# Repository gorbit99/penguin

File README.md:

# Penguin
## A Redox compatible low profile keyboard with per-key RGB

### Parts

- Kailh Choc Switches x 70
- Kailh Choc Keycaps x 70
- Sk6812 mini-e RGB LED\* x 70
- 1n4148 smt sod-123 package diode x 70
- TRRS connector x 2
- 4 pin through-hole tactile switch x 2
- 680 ohm 0608 package resistor\*\* x 2
- Arduino Pro Micro x 2
- TRRS cable x 1
- USB cable for the arduino x 1

\* The type I designed the keyboard for doesn't match the datasheet exactly for
whatever reason, [try getting something that looks like this one](https://www.aliexpress.com/item/4000475685852.html)

\*\* Should work without any resistors if you just bridge their place instead,
but no guarantees

### Keymaps

Should work with any keymap that was made for the redox series.

### Assembly

The keyboard PCB, just like the Redox PCB is double sided. The only component
that goes on the backside are the diodes. This was done to make the board itself
as thin as possible. The rest of the components mount on the topside.

Start with the microcontroller, the resistor and the RGBs. This is necessary,
because soldering the RGB LEDs can be finicky and you'll want a way to test if
you've connected them successfully, which can be done by flashing the
microcontroller. Check each time that's the switches can sit flush on top of the
LEDs, otherwise the whole switch might end up crooked. 

Afterwards it's best to go from smallest to biggest like usual, first the diodes
on the back, then the tactile switch and the TRRS connector and finally the
switches themselves.

### Flashing

By default the keyboard is set to use EEPROM handedness check, this means that
for the first time for both halves the following commands need to be used:

```
make penguin:default:avrdude-split-left
make penguin:default:avrdude-split-right
```

afterwards the end part can be dropped, when flashing again.

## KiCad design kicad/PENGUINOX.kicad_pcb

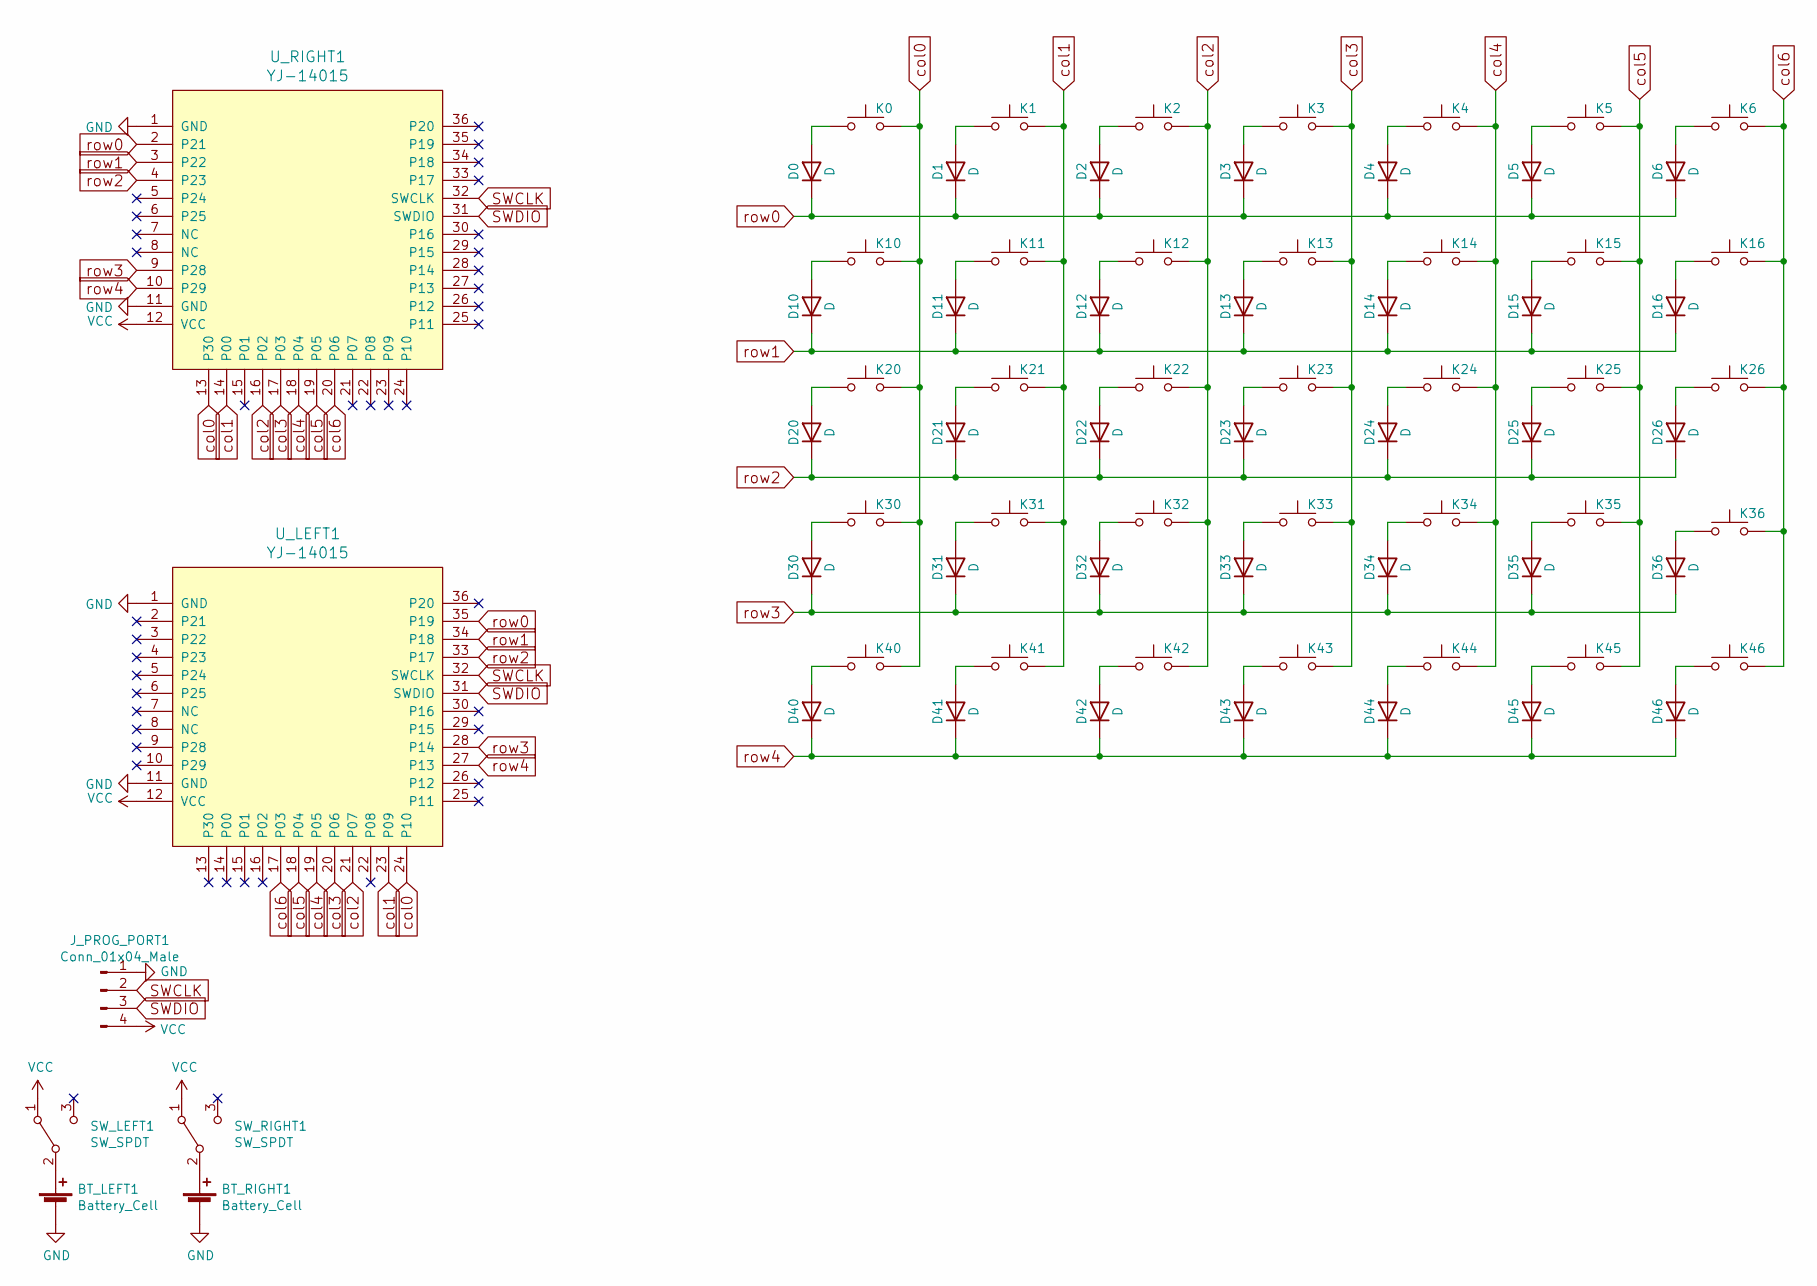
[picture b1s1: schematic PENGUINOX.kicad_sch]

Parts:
BT_LEFT1: Battery_Cell; BatteryHolder_Keystone_3034_1x20mm_bigger_pads
BT_RIGHT1: Battery_Cell; BatteryHolder_Keystone_3034_1x20mm_bigger_pads
D0, D1, D2, D3, D4, D5, D6, D10, D11, D12, D13, D14, D15, D16, D20, D21, D22, D23, D24, D25, D26, D30, D31, D32, D33, D34, D35, D36, D40, D41, D42, D43, D44, D45, D46: D; Diode-dual
J_PROG_PORT1: Conn_01x04_Male; PinHeader_1x04_P2.54mm_Horizontal
K0, K1, K2, K3, K4, K5, K6, K10, K11, K12, K13, K14, K15, K16, K20, K21, K22, K23, K24, K25, K26, K30, K31, K32, K33, K34, K35, K36, K40, K41, K42, K43, K44, K45, K46: KEYSW; Choc_PG1350_Choc_Spacing_Reversible
SW_LEFT1: SW_SPDT; SW_SPDT_PCM12
SW_RIGHT1: SW_SPDT; SW_SPDT_PCM12
U_LEFT1: YJ-14015
U_RIGHT1: YJ-14015

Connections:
GND: BT_LEFT1.2 (-), BT_RIGHT1.2 (-), J_PROG_PORT1.1, U_LEFT1.1 (GND), U_LEFT1.11 (GND), U_RIGHT1.1 (GND), U_RIGHT1.11 (GND)
unnamed: BT_LEFT1.1 (+), SW_LEFT1.2 (B)
unnamed: BT_RIGHT1.1 (+), SW_RIGHT1.2 (B)
unnamed: D0.2 (A), K0.1
unnamed: D1.2 (A), K1.1
unnamed: D2.2 (A), K2.1
unnamed: D3.2 (A), K3.1
unnamed: D4.2 (A), K4.1
unnamed: D5.2 (A), K5.1
unnamed: D6.2 (A), K6.1
unnamed: D10.2 (A), K10.1
unnamed: D11.2 (A), K11.1
unnamed: D12.2 (A), K12.1
unnamed: D13.2 (A), K13.1
unnamed: D14.2 (A), K14.1
unnamed: D15.2 (A), K15.1
unnamed: D16.2 (A), K16.1
unnamed: D20.2 (A), K20.1
unnamed: D21.2 (A), K21.1
unnamed: D22.2 (A), K22.1
unnamed: D23.2 (A), K23.1
unnamed: D24.2 (A), K24.1
unnamed: D25.2 (A), K25.1
unnamed: D26.2 (A), K26.1
unnamed: D30.2 (A), K30.1
unnamed: D31.2 (A), K31.1
unnamed: D32.2 (A), K32.1
unnamed: D33.2 (A), K33.1
unnamed: D34.2 (A), K34.1
unnamed: D35.2 (A), K35.1
unnamed: D36.2 (A), K36.1
unnamed: D40.2 (A), K40.1
unnamed: D41.2 (A), K41.1
unnamed: D42.2 (A), K42.1
unnamed: D43.2 (A), K43.1
unnamed: D44.2 (A), K44.1
unnamed: D45.2 (A), K45.1
unnamed: D46.2 (A), K46.1
SWCLK: J_PROG_PORT1.2, U_LEFT1.32 (SWCLK), U_RIGHT1.32 (SWCLK)
SWDIO: J_PROG_PORT1.3, U_LEFT1.31 (SWDIO), U_RIGHT1.31 (SWDIO)
VCC: J_PROG_PORT1.4, SW_LEFT1.1 (A), SW_RIGHT1.1 (A), U_LEFT1.12 (VCC), U_RIGHT1.12 (VCC)
col0: K0.2, K10.2, K20.2, K30.2, K40.2, U_LEFT1.24 (P10), U_RIGHT1.13 (P30)
col1: K1.2, K11.2, K21.2, K31.2, K41.2, U_LEFT1.23 (P09), U_RIGHT1.14 (P00)
col2: K2.2, K12.2, K22.2, K32.2, K42.2, U_LEFT1.21 (P07), U_RIGHT1.16 (P02)
col3: K3.2, K13.2, K23.2, K33.2, K43.2, U_LEFT1.20 (P06), U_RIGHT1.17 (P03)
col4: K4.2, K14.2, K24.2, K34.2, K44.2, U_LEFT1.19 (P05), U_RIGHT1.18 (P04)
col5: K5.2, K15.2, K25.2, K35.2, K45.2, U_LEFT1.18 (P04), U_RIGHT1.19 (P05)
col6: K6.2, K16.2, K26.2, K36.2, K46.2, U_LEFT1.17 (P03), U_RIGHT1.20 (P06)
row0: D0.1 (K), D1.1 (K), D2.1 (K), D3.1 (K), D4.1 (K), D5.1 (K), D6.1 (K), U_LEFT1.35 (P19), U_RIGHT1.2 (P21)
row1: D10.1 (K), D11.1 (K), D12.1 (K), D13.1 (K), D14.1 (K), D15.1 (K), D16.1 (K), U_LEFT1.34 (P18), U_RIGHT1.3 (P22)
row2: D20.1 (K), D21.1 (K), D22.1 (K), D23.1 (K), D24.1 (K), D25.1 (K), D26.1 (K), U_LEFT1.33 (P17), U_RIGHT1.4 (P23)
row3: D30.1 (K), D31.1 (K), D32.1 (K), D33.1 (K), D34.1 (K), D35.1 (K), D36.1 (K), U_LEFT1.28 (P14), U_RIGHT1.9 (P28)
row4: D40.1 (K), D41.1 (K), D42.1 (K), D43.1 (K), D44.1 (K), D45.1 (K), D46.1 (K), U_LEFT1.27 (P13), U_RIGHT1.10 (P29)

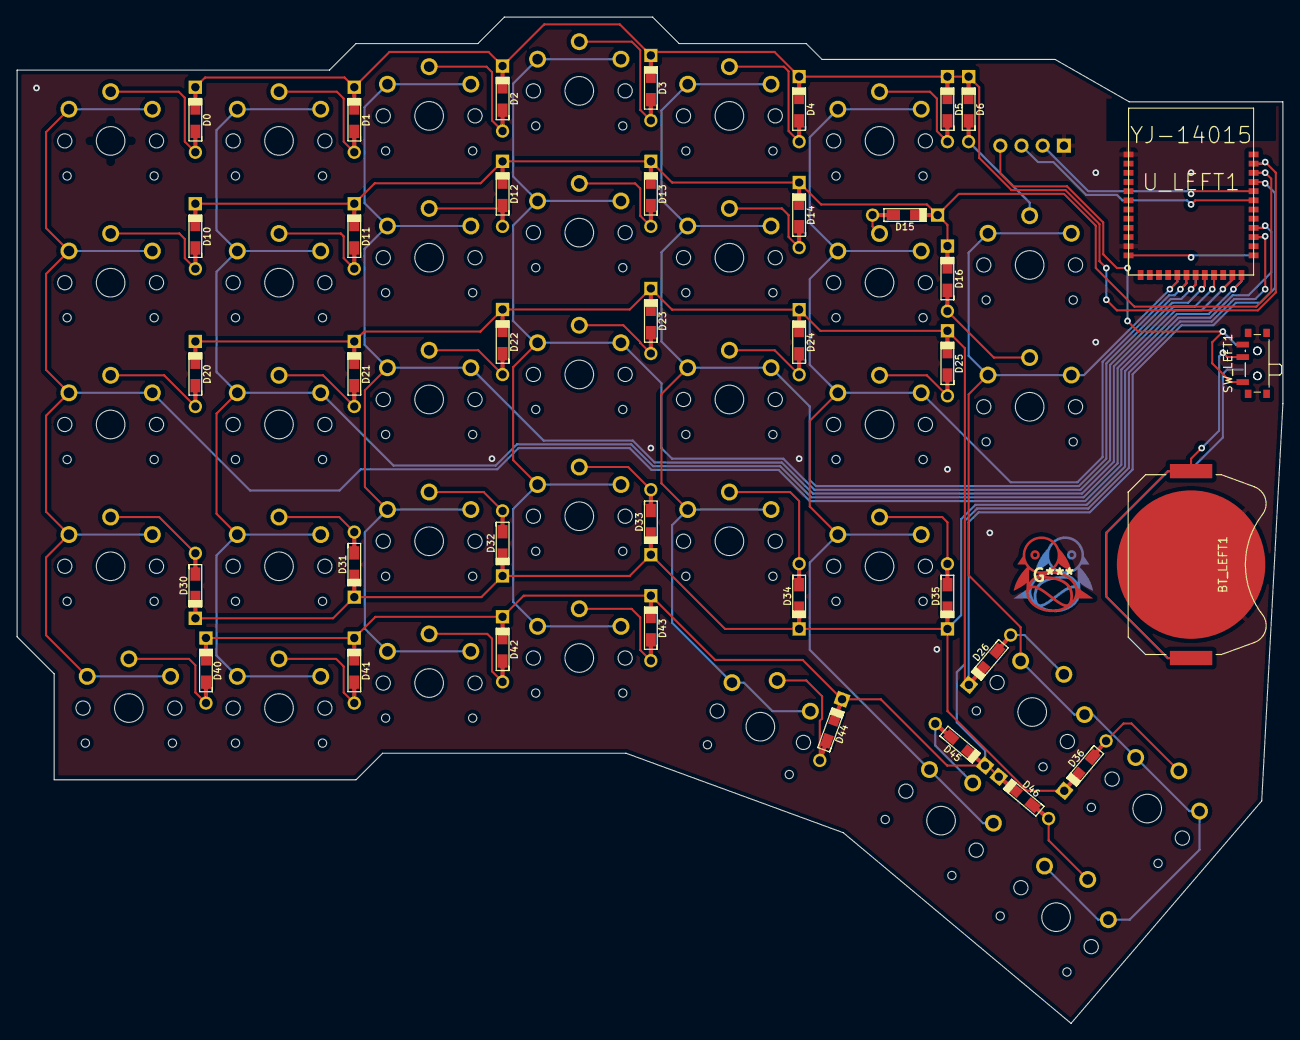
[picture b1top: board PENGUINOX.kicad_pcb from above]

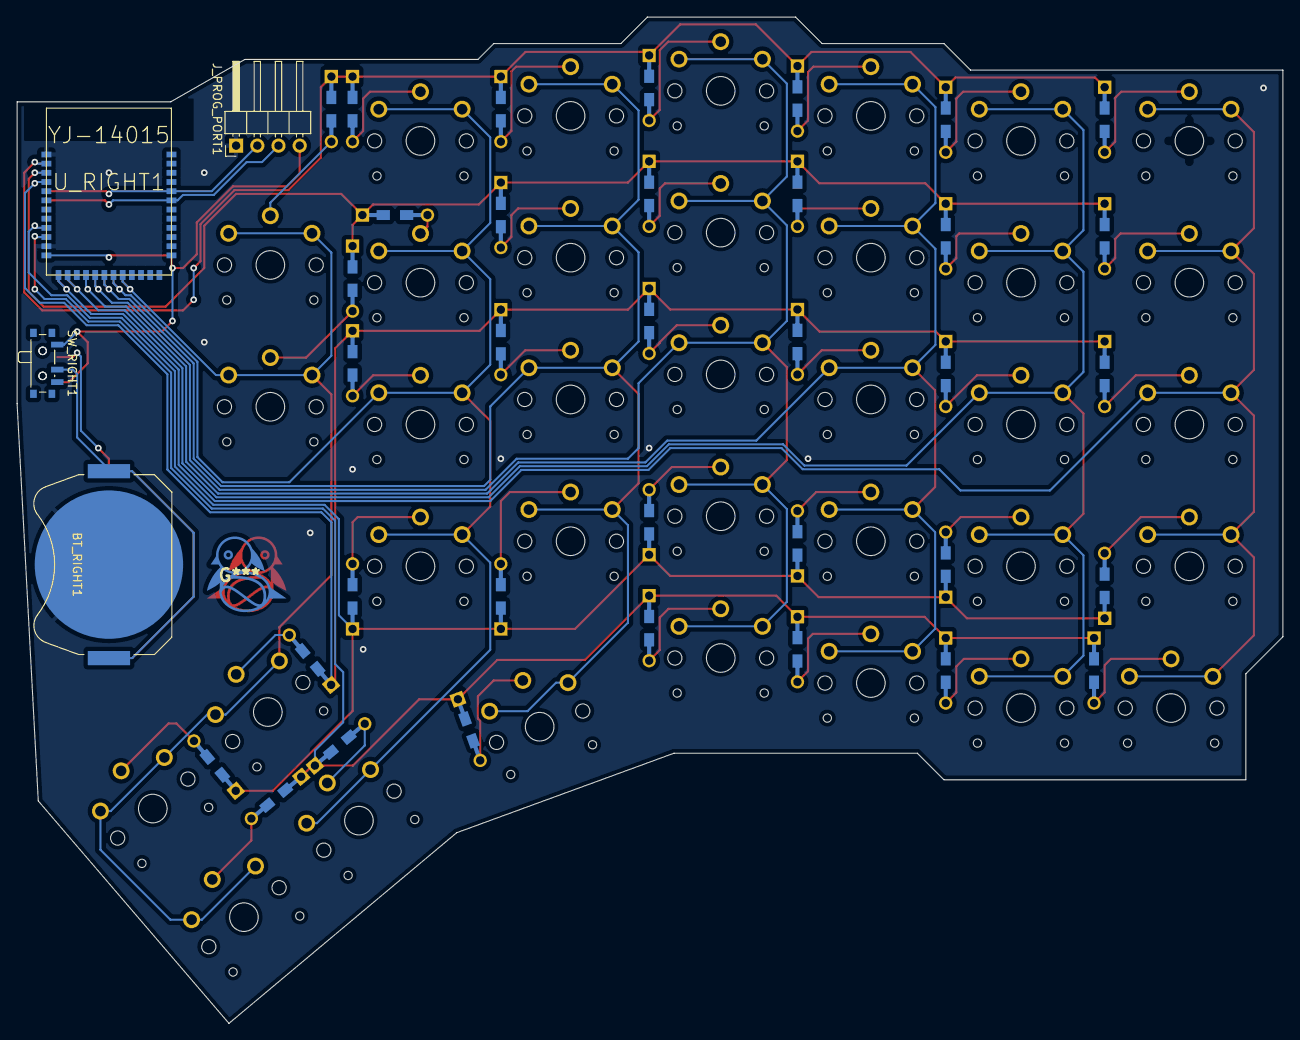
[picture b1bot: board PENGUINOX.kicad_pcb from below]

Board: 2 copper layers, 151.8 x 120.7 mm, 77 parts (4 on the bottom side), 53 nets.

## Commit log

2022-07-28 Initial
2022-07-28 README
2022-10-25 Penguin + Redox = Wireless Penguinox
    Penguin + Redox = Wireless Penguinox
